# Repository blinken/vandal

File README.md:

# vandal
### A lighting and fan control system for campervans (or anything else)

vandal is an ESP32-based 10-channel smart switch module with LoRa, CANBus, a
display, and a rotary encoder. For 12-24V DC systems, intended to control
camper or RV lighting. It features

 * 7 switched-positive output channels, capable of each sourcing 5A at Vin (up to 27V) . All channels support fade, blink, breathe modes via an SX1509 driver.
 * 3 switched-negative channels, capable of each sinking 200mA at up to 30V.
 * 6 protected IO lines, 5V-tolerant and operating at a 3.3V logic level
 * CANBus interface (via a SN65HVD230 transceiver)
 * Protected 1Wire bus, operating at 5V, for temperature sensors (DS1820B and others)
 * LoRa transceiver (HopeRF RFM95) with SMA antenna connection
 * USB programming for the ESP32 (using a FT232R)
 * Numeric/text display: footprints and headers to support 2x [Adafruit 0.54" LED backpacks](https://learn.adafruit.com/adafruit-led-backpack/0-54-alphanumeric) 
 * 8x32 LED matrix: footprints and headers to support 4x MAX7219-based 8x8 LED arrays [Amazon](https://amzn.to/3kYg7Mb) [AliExpress 1](https://www.aliexpress.com/item/32580532205.html) [AliExpress 2](https://www.aliexpress.com/item/33038259447.html)
 * Rotary (quadrature) encoder to allow control by the user
 * Protected power supply supporting 12V and 24V lead-acid and LiFePO4 battery systems

Protected lines feature diode clamping to 5V and 0V, and high-current lines
include TVS diodes on the output to protect against overvoltage and back-EMF.
The input has reverse polarity protection. All outputs (and the input) are
individually fused.

This project is a work in progress, and the software for the ESP32 doesn't
exist yet. It's intended to control LED lighting in my van, and is a bit of an
excuse to play with CANBus and the RFM95 LoRa module.

The PCB was created in KiCad. I have a few spare - if you're interested, [shoot
me an email](mailto:blinken@gmail.com) and I can post you one for a small fee.
Alternatively, the gerber files are available [here](https://github.com/blinken/vandal/blob/main/pcb/van-1.0-gerber/van.zip).

The hardware and software for this project are copyright 2020 Patrick Coleman.
They are released under the GNU General Public License, version 3.0.

## Schematic and board renders

See this [spreadsheet](https://docs.google.com/spreadsheets/d/1M1I1nklSd06B-7MHDgoApl8QgARcywJm6RRHqY701iw/edit?usp=sharing) for the BOM for board revision v1.0.

[Full size PNG](https://raw.githubusercontent.com/blinken/vandal/main/pcb/renders/schematic.png) [PDF](https://github.com/blinken/vandal/raw/main/pcb/renders/schematic.pdf)

[Full size PNG](https://raw.githubusercontent.com/blinken/vandal/main/pcb/renders/v1.0-top.png)

[Full size PNG](https://raw.githubusercontent.com/blinken/vandal/main/pcb/renders/v1.0-bottom.png)

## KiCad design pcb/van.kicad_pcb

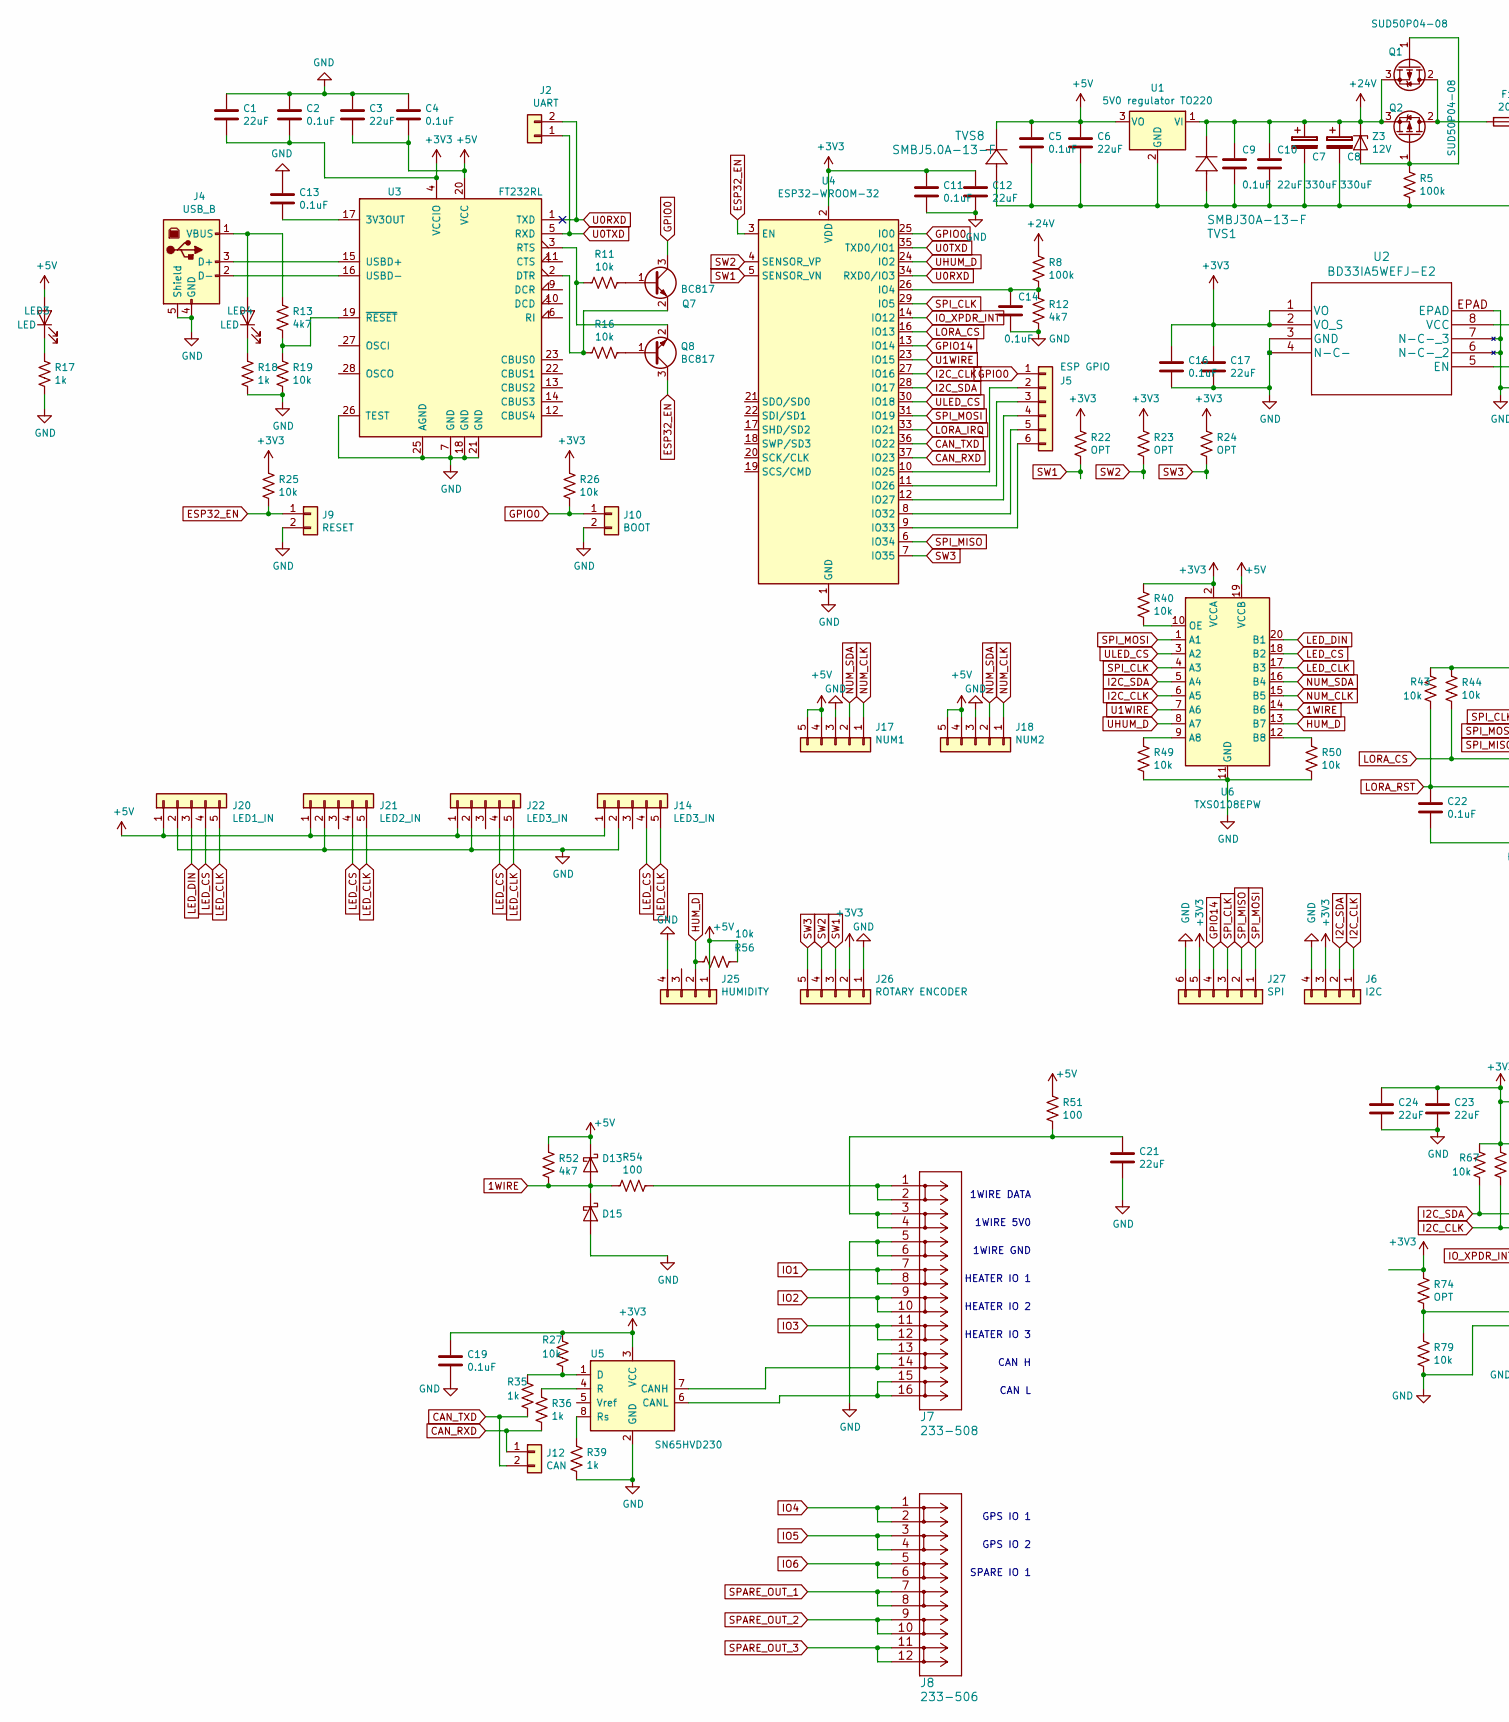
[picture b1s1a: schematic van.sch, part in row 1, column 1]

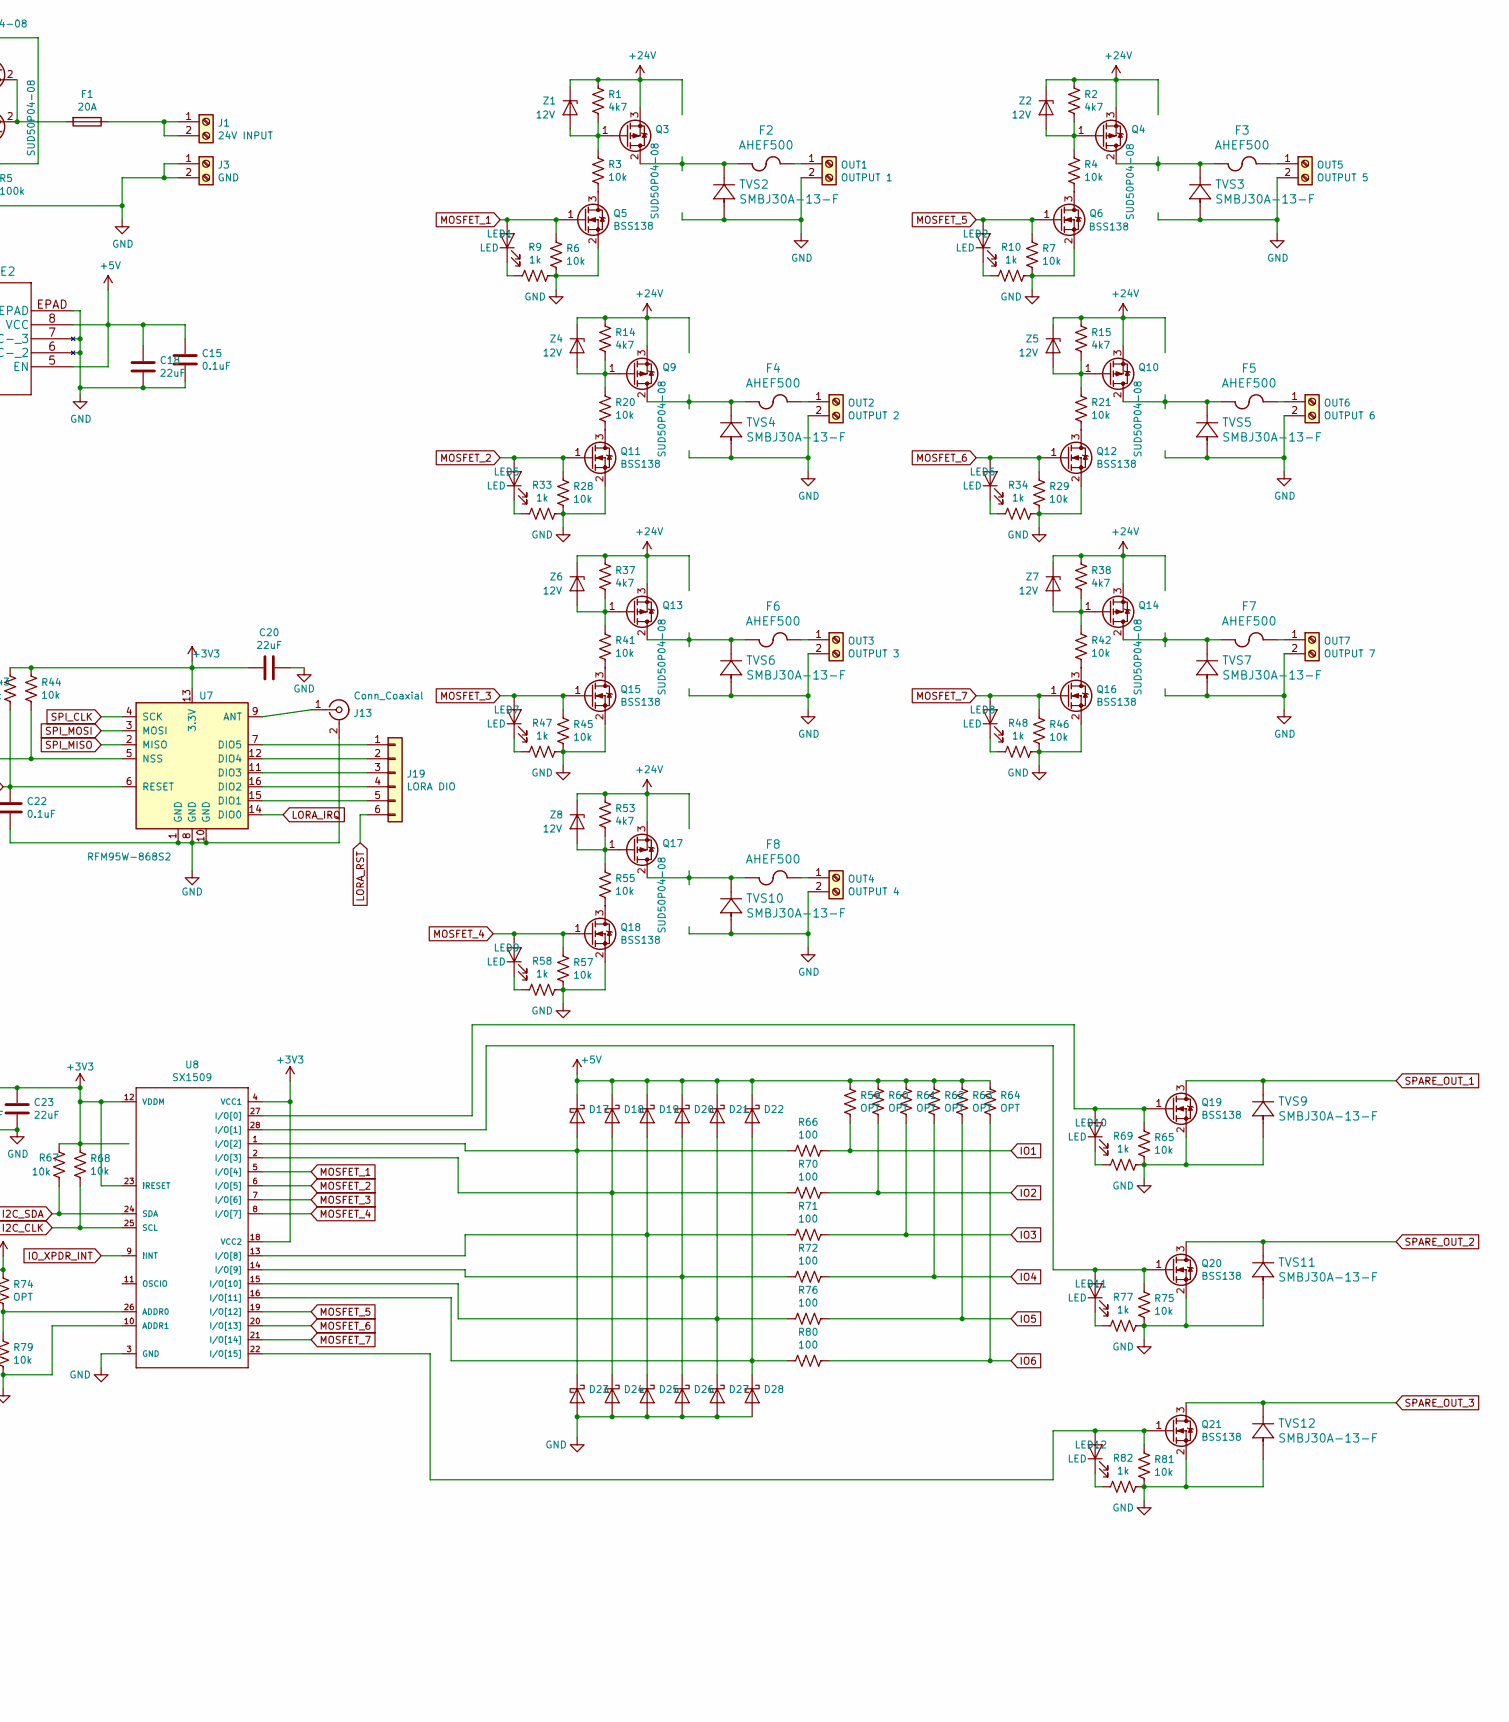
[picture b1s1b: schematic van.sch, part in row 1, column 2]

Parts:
C1, C3, C6, C10, C12, C17, C18, C20, C21, C23, C24: 22uF; C_1206_3216Metric
C2, C4, C5, C9, C11, C13, C14, C15, C16, C19, C22: 0.1uF; C_1206_3216Metric
C7, C8: 330uF; CP_Radial_D10.0mm_P5.00mm
D13, D15, D17, D18, D19, D20, D21, D22, D23, D24, D25, D26, D27, D28: D_Schottky; D_SOD-323_HandSoldering
F1: 20A; Fuseholder_Blade_ATO_Littelfuse_Pudenz_2_Pin
F2, F3, F4, F5, F6, F7, F8: AHEF500
J1: 24V INPUT; TerminalBlock_bornier-2_P5.08mm
J2: UART; PinHeader_1x02_P2.54mm_Vertical
J3: GND; TerminalBlock_bornier-2_P5.08mm
J4: USB_B; USB_B_OST_USB-B1HSxx_Horizontal
J5: ESP GPIO; PinHeader_1x06_P2.54mm_Vertical
J6: I2C; PinHeader_1x04_P2.54mm_Vertical
J7: 233-508
J8: 233-506
J9: RESET; PinHeader_1x02_P2.54mm_Vertical
J10: BOOT; PinHeader_1x02_P2.54mm_Vertical
J12: CAN; PinHeader_1x02_P2.54mm_Vertical
J13: Conn_Coaxial; SMA_Amphenol_132134_Vertical
J14, J22: LED3_IN; PinHeader_1x05_P2.54mm_Vertical
J17: NUM1; PinHeader_1x05_P2.54mm_Vertical
J18: NUM2; PinHeader_1x05_P2.54mm_Vertical
J19: LORA DIO; PinHeader_1x06_P2.54mm_Vertical
J20: LED1_IN; PinHeader_1x05_P2.54mm_Vertical
J21: LED2_IN; PinHeader_1x05_P2.54mm_Vertical
J25: HUMIDITY; PinHeader_1x04_P2.54mm_Vertical
J26: ROTARY ENCODER; PinHeader_1x05_P2.54mm_Vertical
J27: SPI; PinHeader_1x06_P2.54mm_Vertical
LED1, LED2, LED3, LED4, LED5, LED6, LED7, LED8, LED9, LED10, LED11, LED12: LED; LED_1206_3216Metric
OUT1: OUTPUT 1; TerminalBlock_bornier-2_P5.08mm
OUT2: OUTPUT 2; TerminalBlock_bornier-2_P5.08mm
OUT3: OUTPUT 3; TerminalBlock_bornier-2_P5.08mm
OUT4: OUTPUT 4; TerminalBlock_bornier-2_P5.08mm
OUT5: OUTPUT 5; TerminalBlock_bornier-2_P5.08mm
OUT6: OUTPUT 6; TerminalBlock_bornier-2_P5.08mm
OUT7: OUTPUT 7; TerminalBlock_bornier-2_P5.08mm
Q1, Q2, Q3, Q4, Q9, Q10, Q13, Q14, Q17: SUD50P04-08; TO-252-2
Q5, Q6, Q11, Q12, Q15, Q16, Q18, Q19, Q20, Q21: BSS138; SOT-23
Q7, Q8: BC817; SOT-23
R1, R2, R12, R13, R14, R15, R37, R38, R52, R53: 4k7; R_1206_3216Metric_Pad1.42x1.75mm_HandSolder
R3, R4, R6, R7, R11, R16, R19, R20, R21, R25, R26, R27, R28, R29, R40, R41, R42, R43, R44, R45, R46, R49, R50, R55, R56, R57, R65, R67, R68, R75, R79, R81: 10k; R_1206_3216Metric_Pad1.42x1.75mm_HandSolder
R5, R8: 100k; R_1206_3216Metric_Pad1.42x1.75mm_HandSolder
R9, R10, R17, R18, R33, R34, R35, R36, R39, R47, R48, R58, R69, R77, R82: 1k; R_1206_3216Metric_Pad1.42x1.75mm_HandSolder
R22, R23, R24, R59, R60, R61, R62, R63, R64, R74: OPT; R_1206_3216Metric_Pad1.42x1.75mm_HandSolder
R51, R54, R66, R70, R71, R72, R76, R80: 100; R_1206_3216Metric_Pad1.42x1.75mm_HandSolder
TVS1, TVS2, TVS3, TVS4, TVS5, TVS6, TVS7, TVS9, TVS10, TVS11, TVS12: SMBJ30A-13-F
TVS8: SMBJ5.0A-13-F; SMBJ5.0A-E3&slash_52
U1: 5V0 regulator TO220; TO-220-3_Vertical
U2: BD33IA5WEFJ-E2
U3: FT232RL; SSOP-28_5.3x10.2mm_P0.65mm
U4: ESP32-WROOM-32
U5: SN65HVD230; SOIC-8_3.9x4.9mm_P1.27mm
U6: TXS0108EPW; TSSOP-20_4.4x6.5mm_P0.65mm
U7: RFM95W-868S2; HOPERF_RFM9XW_SMD
U8: SX1509; QFN-28
Z1, Z2, Z3, Z4, Z5, Z6, Z7, Z8: 12V; D_SOD-323_HandSoldering

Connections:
1WIRE: D13.2 (A), D15.1 (K), R52.2, R54.2, U6.14 (B6)
+3V3: C1.2, C2.2, C11.1, C12.1, C16.1, C17.1, C19.1, C20.2, C23.2, C24.2, J6.3, J26.2, J27.5, R22.2, R23.2, R24.2, R25.2, R26.2, R27.1, R40.1, R43.1, R44.1, R67.2, R68.2, R74.2, U2.1 (VO), U2.2 (VO_S), U3.4 (VCCIO), U4.2 (VDD), U5.3 (VCC), U6.2 (VCCA), U7.13 (3.3V), U8.4 (VCC1), U8.12 (VDDM), U8.18 (VCC2), U8.23 (!RESET)
+5V: C3.2, C4.2, C5.1, C6.1, C15.1, C18.1, D13.1 (K), D17.1 (K), D18.1 (K), D19.1 (K), D20.1 (K), D21.1 (K), D22.1 (K), J14.1, J17.4, J17.5, J18.4, J18.5, J20.1, J21.1, J22.1, J25.1, LED3.2 (A), R51.2, R52.1, R56.1, R59.2, R60.2, R61.2, R62.2, R63.2, R64.2, TVS8.1, U1.3 (VO), U2.5 (EN), U2.8 (VCC), U3.20 (VCC), U6.19 (VCCB)
+24V: C7.1, C8.1, C9.1, C10.1, Q1.3 (S), Q2.3 (S), Q3.3 (S), Q4.3 (S), Q9.3 (S), Q10.3 (S), Q13.3 (S), Q14.3 (S), Q17.3 (S), R1.1, R2.1, R8.1, R14.1, R15.1, R37.1, R38.1, R53.1, TVS1.1, U1.1 (VI), Z1.1 (K), Z2.1 (K), Z3.1 (K), Z4.1 (K), Z5.1 (K), Z6.1 (K), Z7.1 (K), Z8.1 (K)
CAN_RXD: J12.1, R36.2, U4.37 (IO23)
CAN_TXD: J12.2, R35.2, U4.36 (IO22)
ESP32_EN: J9.1, Q8.3 (C), R25.1, U4.3 (EN)
GND: C1.1, C2.1, C3.1, C4.1, C5.2, C6.2, C7.2, C8.2, C9.2, C10.2, C11.2, C12.2, C13.1, C14.2, C15.2, C16.2, C17.2, C18.2, C19.2, C20.1, C21.1, C22.2, C23.1, C24.1, D15.2 (A), D23.2 (A), D24.2 (A), D25.2 (A), D26.2 (A), D27.2 (A), D28.2 (A), J3.1, J3.2, J4.4 (GND), J4.5 (Shield), J6.4, J7.5, J7.6, J9.2, J10.2, J13.2 (Ext), J14.2, J17.3, J18.3, J20.2, J21.2, J22.2, J25.4, J26.1, J27.6, OUT1.2, OUT2.2, OUT3.2, OUT4.2, OUT5.2, OUT6.2, OUT7.2, Q5.2 (S), Q6.2 (S), Q11.2 (S), Q12.2 (S), Q15.2 (S), Q16.2 (S), Q18.2 (S), Q19.2 (S), Q20.2 (S), Q21.2 (S), R5.1, R6.2, R7.2, R9.1, R10.1, R12.2, R17.1, R18.1, R19.1, R28.2, R29.2, R33.1, R34.1, R39.2, R45.2, R46.2, R47.1, R48.1, R49.2, R50.2, R57.2, R58.1, R65.2, R69.1, R75.2, R77.1, R79.1, R81.2, R82.1, TVS1.2, TVS2.2, TVS3.2, TVS4.2, TVS5.2, TVS6.2, TVS7.2, TVS8.2, TVS9.2, TVS10.2, TVS11.2, TVS12.2, U1.2 (GND), U2.3 (GND), U2.4 (N-C-), U2.6 (N-C-_2), U2.7 (N-C-_3), U2.EPAD, U3.7 (GND), U3.18 (GND), U3.21 (GND), U3.25 (AGND), U3.26 (TEST), U4.1 (GND), U4.15 (GND), U4.38 (GND), U4.39, U5.2 (GND), U6.11 (GND), U7.1 (GND), U7.8 (GND), U7.10 (GND), U8.3 (GND), U8.10 (ADDR1), U8.17 (GND), U8.29 (GND)
GPIO0: J5.1, J10.1, Q7.3 (C), R26.1, U4.25 (IO0)
GPIO14: J27.4, U4.13 (IO14)
HUM_D: J25.2, R56.2, U6.13 (B7)
I2C_CLK: J6.1, R68.1, U4.27 (IO16), U6.6 (A5), U8.25 (SCL)
I2C_SDA: J6.2, R67.1, U4.28 (IO17), U6.5 (A4), U8.24 (SDA)
IO1: J7.7, J7.8, R59.1, R66.1
IO2: J7.9, J7.10, R60.1, R70.1
IO3: J7.11, J7.12, R61.1, R71.1
IO4: J8.1, J8.2, R62.1, R72.1
IO5: J8.3, J8.4, R63.1, R76.1
IO6: J8.5, J8.6, R64.1, R80.1
IO_XPDR_INT: U4.14 (IO12), U8.9 (!INT)
LED_CLK: J14.5, J20.5, J21.5, J22.5, U6.17 (B3)
LED_CS: J14.4, J20.4, J21.4, J22.4, U6.18 (B2)
LED_DIN: J20.3, U6.20 (B1)
LORA_CS: R44.2, U4.16 (IO13), U7.5 (NSS)
LORA_IRQ: U4.33 (IO21), U7.14 (DIO0)
LORA_RST: C22.1, J19.6, R43.2, U7.6 (RESET)
MOSFET_1: LED1.2 (A), Q5.1 (G), R6.1, U8.5 (I/O[4])
MOSFET_2: LED5.2 (A), Q11.1 (G), R28.1, U8.6 (I/O[5])
MOSFET_3: LED7.2 (A), Q15.1 (G), R45.1, U8.7 (I/O[6])
MOSFET_4: LED9.2 (A), Q18.1 (G), R57.1, U8.8 (I/O[7])
MOSFET_5: LED2.2 (A), Q6.1 (G), R7.1, U8.19 (I/O[12])
MOSFET_6: LED6.2 (A), Q12.1 (G), R29.1, U8.20 (I/O[13])
MOSFET_7: LED8.2 (A), Q16.1 (G), R46.1, U8.21 (I/O[14])
NUM_CLK: J17.1, J18.1, U6.15 (B5)
NUM_SDA: J17.2, J18.2, U6.16 (B4)
unnamed: C13.2, U3.17 (3V3OUT)
unnamed: C14.1, R8.2, R12.1, U4.26 (IO4)
unnamed: C21.2, J7.3, J7.4, R51.1
unnamed: D17.2 (A), D23.1 (K), R66.2, U8.1 (I/O[2])
unnamed: D18.2 (A), D24.1 (K), R70.2, U8.2 (I/O[3])
unnamed: D19.2 (A), D25.1 (K), R71.2, U8.13 (I/O[8])
unnamed: D20.2 (A), D26.1 (K), R72.2, U8.14 (I/O[9])
unnamed: D21.2 (A), D27.1 (K), R76.2, U8.15 (I/O[10])
unnamed: D22.2 (A), D28.1 (K), R80.2, U8.16 (I/O[11])
unnamed: F1.1, J1.1, J1.2
unnamed: F1.2, Q1.2 (D), Q2.2 (D)
unnamed: F2.1, Q3.2 (D), TVS2.1
unnamed: F2.2, OUT1.1
unnamed: F3.1, Q4.2 (D), TVS3.1
unnamed: F3.2, OUT5.1
unnamed: F4.1, Q9.2 (D), TVS4.1
unnamed: F4.2, OUT2.1
unnamed: F5.1, Q10.2 (D), TVS5.1
unnamed: F5.2, OUT6.1
unnamed: F6.1, Q13.2 (D), TVS6.1
unnamed: F6.2, OUT3.1
unnamed: F7.1, Q14.2 (D), TVS7.1
unnamed: F7.2, OUT7.1
unnamed: F8.1, Q17.2 (D), TVS10.1
unnamed: F8.2, OUT4.1
unnamed: J4.1 (VBUS), LED4.2 (A), R13.2
unnamed: J4.2 (D-), U3.16 (USBD-)
unnamed: J4.3 (D+), U3.15 (USBD+)
unnamed: J5.2, U4.10 (IO25)
unnamed: J5.3, U4.11 (IO26)
unnamed: J5.4, U4.12 (IO27)
unnamed: J5.5, U4.8 (IO32)
unnamed: J5.6, U4.9 (IO33)
unnamed: J7.1, J7.2, R54.1
unnamed: J7.13, J7.14, U5.7 (CANH)
unnamed: J7.15, J7.16, U5.6 (CANL)
unnamed: J13.1 (In), U7.9 (ANT)
unnamed: J19.1, U7.7 (DIO5)
unnamed: J19.2, U7.12 (DIO4)
unnamed: J19.3, U7.11 (DIO3)
unnamed: J19.4, U7.16 (DIO2)
unnamed: J19.5, U7.15 (DIO1)
unnamed: LED1.1 (K), R9.2
unnamed: LED2.1 (K), R10.2
unnamed: LED3.1 (K), R17.2
unnamed: LED4.1 (K), R18.2
unnamed: LED5.1 (K), R33.2
unnamed: LED6.1 (K), R34.2
unnamed: LED7.1 (K), R47.2
unnamed: LED8.1 (K), R48.2
unnamed: LED9.1 (K), R58.2
unnamed: LED10.1 (K), R69.2
unnamed: LED10.2 (A), Q19.1 (G), R65.1, U8.27 (I/O[0])
unnamed: LED11.1 (K), R77.2
unnamed: LED11.2 (A), Q20.1 (G), R75.1, U8.28 (I/O[1])
unnamed: LED12.1 (K), R82.2
unnamed: LED12.2 (A), Q21.1 (G), R81.1, U8.22 (I/O[15])
unnamed: Q1.1 (G), Q2.1 (G), R5.2, Z3.2 (A)
unnamed: Q3.1 (G), R1.2, R3.1, Z1.2 (A)
unnamed: Q4.1 (G), R2.2, R4.1, Z2.2 (A)
unnamed: Q5.3 (D), R3.2
unnamed: Q6.3 (D), R4.2
unnamed: Q7.1 (B), R11.2
unnamed: Q7.2 (E), R16.1, U3.2 (DTR)
unnamed: Q8.1 (B), R16.2
unnamed: Q8.2 (E), R11.1, U3.3 (RTS)
unnamed: Q9.1 (G), R14.2, R20.1, Z4.2 (A)
unnamed: Q10.1 (G), R15.2, R21.1, Z5.2 (A)
unnamed: Q11.3 (D), R20.2
unnamed: Q12.3 (D), R21.2
unnamed: Q13.1 (G), R37.2, R41.1, Z6.2 (A)
unnamed: Q14.1 (G), R38.2, R42.1, Z7.2 (A)
unnamed: Q15.3 (D), R41.2
unnamed: Q16.3 (D), R42.2
unnamed: Q17.1 (G), R53.2, R55.1, Z8.2 (A)
unnamed: Q18.3 (D), R55.2
unnamed: R13.1, R19.2, U3.19 (~RESET~)
unnamed: R27.2, R35.1, U5.1 (D)
unnamed: R36.1, U5.4 (R)
unnamed: R39.1, U5.8 (Rs)
unnamed: R40.2, U6.10 (OE)
unnamed: R49.1, U6.9 (A8)
unnamed: R50.1, U6.12 (B8)
unnamed: R74.1, R79.2, U8.26 (ADDR0)
SPARE_OUT_1: J8.7, J8.8, Q19.3 (D), TVS9.1
SPARE_OUT_2: J8.9, J8.10, Q20.3 (D), TVS11.1
SPARE_OUT_3: J8.11, J8.12, Q21.3 (D), TVS12.1
SPI_CLK: J27.3, U4.29 (IO5), U6.4 (A3), U7.4 (SCK)
SPI_MISO: J27.2, U4.6 (IO34), U7.2 (MISO)
SPI_MOSI: J27.1, U4.31 (IO19), U6.1 (A1), U7.3 (MOSI)
SW1: J26.3, R22.1, U4.5 (SENSOR_VN)
SW2: J26.4, R23.1, U4.4 (SENSOR_VP)
SW3: J26.5, R24.1, U4.7 (IO35)
U0RXD: J2.2, U3.1 (TXD), U4.34 (RXD0/IO3)
U0TXD: J2.1, U3.5 (RXD), U4.35 (TXD0/IO1)
U1WIRE: U4.23 (IO15), U6.7 (A6)
UHUM_D: U4.24 (IO2), U6.8 (A7)
ULED_CS: U4.30 (IO18), U6.3 (A2)

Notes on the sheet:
1WIRE DATA
1WIRE 5V0
1WIRE GND
HEATER IO 1
HEATER IO 2
HEATER IO 3
CAN H
CAN L
GPS IO 1
GPS IO 2
SPARE IO 1

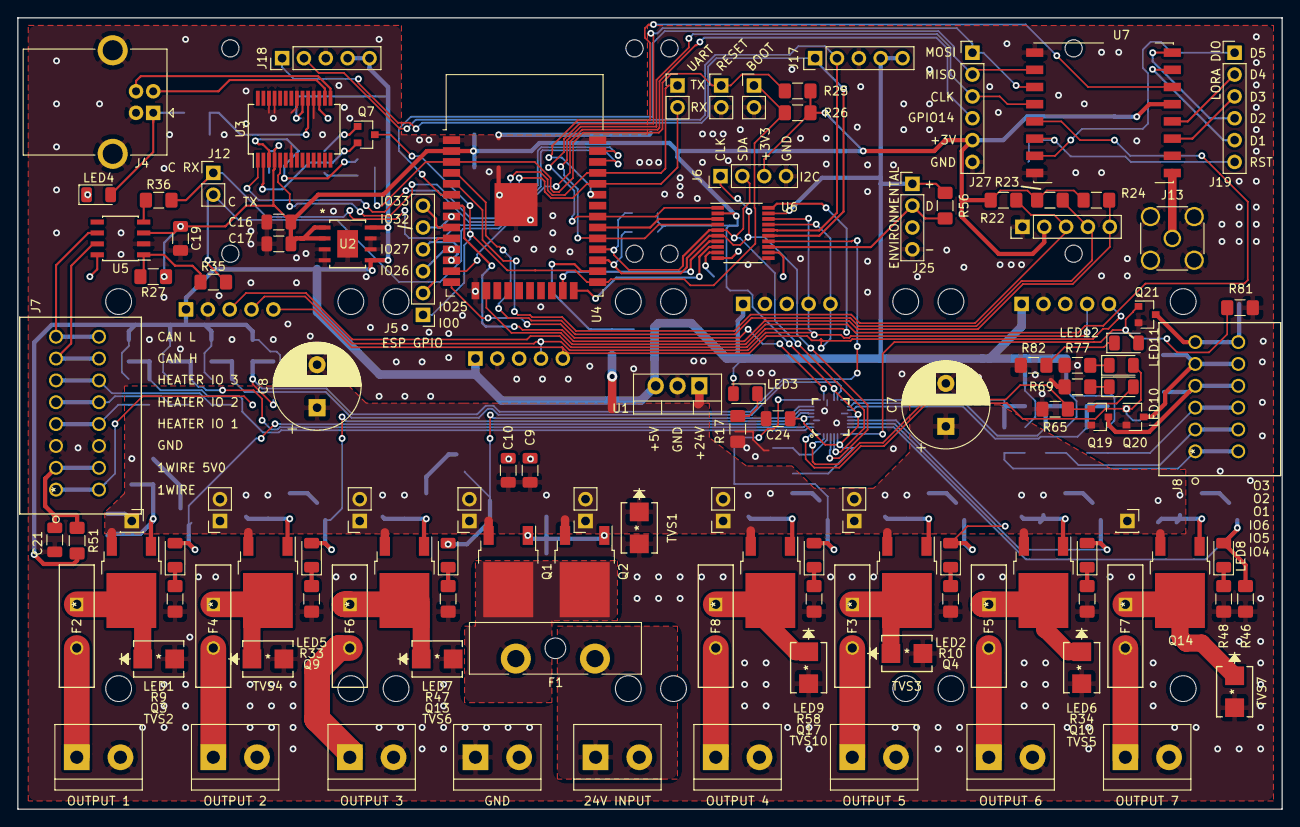
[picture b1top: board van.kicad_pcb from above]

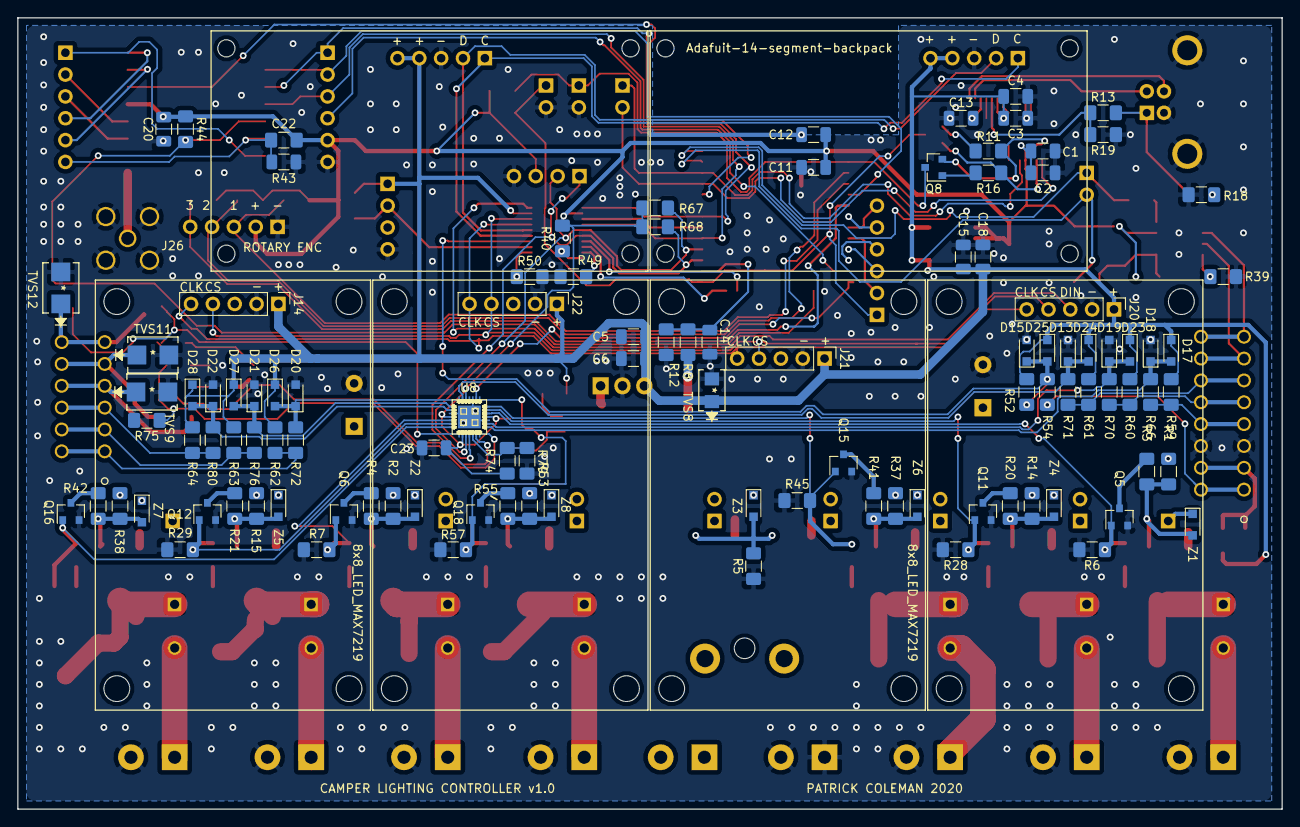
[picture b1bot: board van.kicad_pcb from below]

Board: 2 copper layers, 147.0 x 92.0 mm, 213 parts (107 on the bottom side), 133 nets.

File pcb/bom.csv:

"Id";"Designator";"Package";"Quantity";"Designation";"Supplier and ref";
1;"REF**,REF**,REF**,REF**";"8x8_LED_module";4;"8x8_LED_MAX7219";;;
2;"REF**,REF**";"Adafuit-14-segment-backpack";2;"Adafuit-14-segment-backpack";;;
3;"REF**,REF**,REF**,REF**,REF**,REF**";"PinSocket_1x02_P2.54mm_Vertical";6;"PinSocket_1x02_P2.54mm_Vertical";;;
4;"REF**,REF**";"PinSocket_1x01_P2.54mm_Vertical";2;"PinSocket_1x01_P2.54mm_Vertical";;;
5;"C24,C23,C10,C1,C3,C6,C12,C17,C18,C20,C21";"C_1206_3216Metric";11;"22uF";;;
6;"U8";"QFN-28";1;"SX1509";;;
7;"J6";"PinHeader_1x04_P2.54mm_Vertical";1;"I2C";;;
8;"J5";"PinHeader_1x06_P2.54mm_Vertical";1;"ESP GPIO";;;
9;"D19,D20,D21,D22,D23,D24,D25,D18,D26,D17,D28,D27,D15,D13";"D_SOD-323_HandSoldering";14;"D_Schottky";;;
10;"LED11,LED10,LED12,LED3,LED1,LED5,LED4,LED6,LED7,LED8,LED9,LED2";"LED_1206_3216Metric";12;"LED";;;
11;"Q21,Q20,Q19,Q12,Q11,Q18,Q15,Q6,Q16,Q5";"SOT-23";10;"BSS138";;;
12;"R80,R66,R71,R72,R76,R70,R54,R51";"R_1206_3216Metric_Pad1.42x1.75mm_HandSolder";8;"100";;;
13;"R68,R67,R65,R75,R79,R81,R19,R16,R11,R7,R4,R20,R21,R25,R26,R27,R6,R29,R28,R55,R56,R57,R40,R41,R46,R49,R50,R45,R44,R43,R3,R42";"R_1206_3216Metric_Pad1.42x1.75mm_HandSolder";32;"10k";;;
14;"R60,R61,R62,R63,R64,R59,R74,R22,R23,R24";"R_1206_3216Metric_Pad1.42x1.75mm_HandSolder";10;"OPT";;;
15;"R69,R77,R82,R10,R9,R18,R17,R58,R39,R36,R35,R34,R33,R47,R48";"R_1206_3216Metric_Pad1.42x1.75mm_HandSolder";15;"1k";;;
16;"TVS12,TVS11,TVS9,TVS3,TVS1,TVS2,TVS10,TVS7,TVS6,TVS5,TVS4";"SMBJ30A-13-F";11;"SMBJ30A-13-F";;;
17;"J8";"233-506";1;"233-506";;;
18;"J7";"233-508";1;"233-508";;;
19;"U1";"TO-220-3_Vertical";1;"5V0 regulator TO220";;;
20;"J14,J22";"PinHeader_1x05_P2.54mm_Vertical";2;"LED3_IN";;;
21;"U2";"BD33IA5WEFJ-E2";1;"BD33IA5WEFJ-E2";;;
22;"C2,C4,C5,C9,C11,C13,C14,C15,C16,C19,C22";"C_1206_3216Metric";11;"0.1uF";;;
23;"C8,C7";"CP_Radial_D10.0mm_P5.00mm";2;"330uF";;;
24;"J13";"SMA_Amphenol_132134_Vertical";1;"Conn_Coaxial";;;
25;"J12";"PinHeader_1x02_P2.54mm_Vertical";1;"CAN";;;
26;"J9";"PinHeader_1x02_P2.54mm_Vertical";1;"RESET";;;
27;"J2";"PinHeader_1x02_P2.54mm_Vertical";1;"UART";;;
28;"J10";"PinHeader_1x02_P2.54mm_Vertical";1;"BOOT";;;
29;"J25";"PinHeader_1x04_P2.54mm_Vertical";1;"HUMIDITY";;;
30;"J26";"PinHeader_1x05_P2.54mm_Vertical";1;"ROTARY ENCODER";;;
31;"J17";"PinHeader_1x05_P2.54mm_Vertical";1;"NUM1";;;
32;"J18";"PinHeader_1x05_P2.54mm_Vertical";1;"NUM2";;;
33;"J20";"PinHeader_1x05_P2.54mm_Vertical";1;"LED1_IN";;;
34;"J21";"PinHeader_1x05_P2.54mm_Vertical";1;"LED2_IN";;;
35;"J27";"PinHeader_1x06_P2.54mm_Vertical";1;"SPI";;;
36;"J19";"PinHeader_1x06_P2.54mm_Vertical";1;"LORA DIO";;;
37;"J4";"USB_B_OST_USB-B1HSxx_Horizontal";1;"USB_B";;;
38;"Z5,Z7,Z6,Z4,Z3,Z2,Z1,Z8";"D_SOD-323_HandSoldering";8;"12V";;;
39;"F1";"Fuseholder_Blade_ATO_Littelfuse_Pudenz_2_Pin";1;"20A";;;
40;"U5";"SOIC-8_3.9x4.9mm_P1.27mm";1;"SN65HVD230";;;
41;"U3";"SSOP-28_5.3x10.2mm_P0.65mm";1;"FT232RL";;;
42;"U6";"TSSOP-20_4.4x6.5mm_P0.65mm";1;"TXS0108EPW";;;
43;"Q8,Q7";"SOT-23";2;"BC817";;;
44;"Q9,Q14,Q17,Q10,Q4,Q3,Q2,Q1,Q13";"TO-252-2";9;"SUD50P04-08";;;
45;"U4";"ESP32-WROOM-32";1;"ESP32-WROOM-32";;;
46;"U7";"HOPERF_RFM9XW_SMD";1;"RFM95W-868S2";;;
47;"R15,R1,R13,R12,R14,R53,R38,R37,R52,R2";"R_1206_3216Metric_Pad1.42x1.75mm_HandSolder";10;"4k7";;;
48;"R8,R5";"R_1206_3216Metric_Pad1.42x1.75mm_HandSolder";2;"100k";;;
49;"OUT6";"TerminalBlock_bornier-2_P5.08mm";1;"OUTPUT 6";;;
50;"J3";"TerminalBlock_bornier-2_P5.08mm";1;"GND";;;
51;"OUT5";"TerminalBlock_bornier-2_P5.08mm";1;"OUTPUT 5";;;
52;"J1";"TerminalBlock_bornier-2_P5.08mm";1;"24V INPUT";;;
53;"OUT7";"TerminalBlock_bornier-2_P5.08mm";1;"OUTPUT 7";;;
54;"OUT4";"TerminalBlock_bornier-2_P5.08mm";1;"OUTPUT 4";;;
55;"OUT3";"TerminalBlock_bornier-2_P5.08mm";1;"OUTPUT 3";;;
56;"OUT2";"TerminalBlock_bornier-2_P5.08mm";1;"OUTPUT 2";;;
57;"OUT1";"TerminalBlock_bornier-2_P5.08mm";1;"OUTPUT 1";;;
58;"TVS8";"SMBJ5.0A-E3&slash_52";1;"SMBJ5.0A-13-F";;;
59;"F2,F8,F7,F6,F4,F3,F5";"AHEF500";7;"AHEF500";;;

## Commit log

2020-11-23 vandal, initial commit
    Import platformio framework and PCB layout for board rev 1.0. Add a
    simple README, some board renders, and the schematic.
2020-11-23 readme, add board renders and schematic
2020-11-23 pcb, add v1.0 BOM
2020-11-23 readme, remove unnecessary header
2020-11-23 readme, mention the rotary encoder
2020-11-24 pcb, fix NPTH on paste layers
    The solderpaste layers incorrectly contained NPTH for mounting the
    modules, which jlcpcb picked up. Fix the two footprints and revise the
    two paste layers.
2020-12-11 wrangling i2c bus things - some communication working
2020-12-11 working LED driver with each mode demonstrated
    The one-shot mode seems a bit useless - it must be designed for an
    inverted output.
2020-12-11 remove unnecessary comments
2020-12-13 rotary encoder, count using pulse counter module
    Use the hardware pulse counter to process the quadrature encoder.
    Examples cribbed from the ESP32 example solution.
    Note - the interrupt routine doesn't work yet (LoadProhibited crash loop
    when enabled).
    The filter value seems to need to be very high in order to miss stray
    counts.
2021-02-25 merge some maybe-broken changes to add support for the LED panel, but do not work yet.
    edit - these did work... there was a dry solder joint. Yay!

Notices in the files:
parts and their libraries:
Copyright 2016 Accelerated Designs. All rights reserved.
